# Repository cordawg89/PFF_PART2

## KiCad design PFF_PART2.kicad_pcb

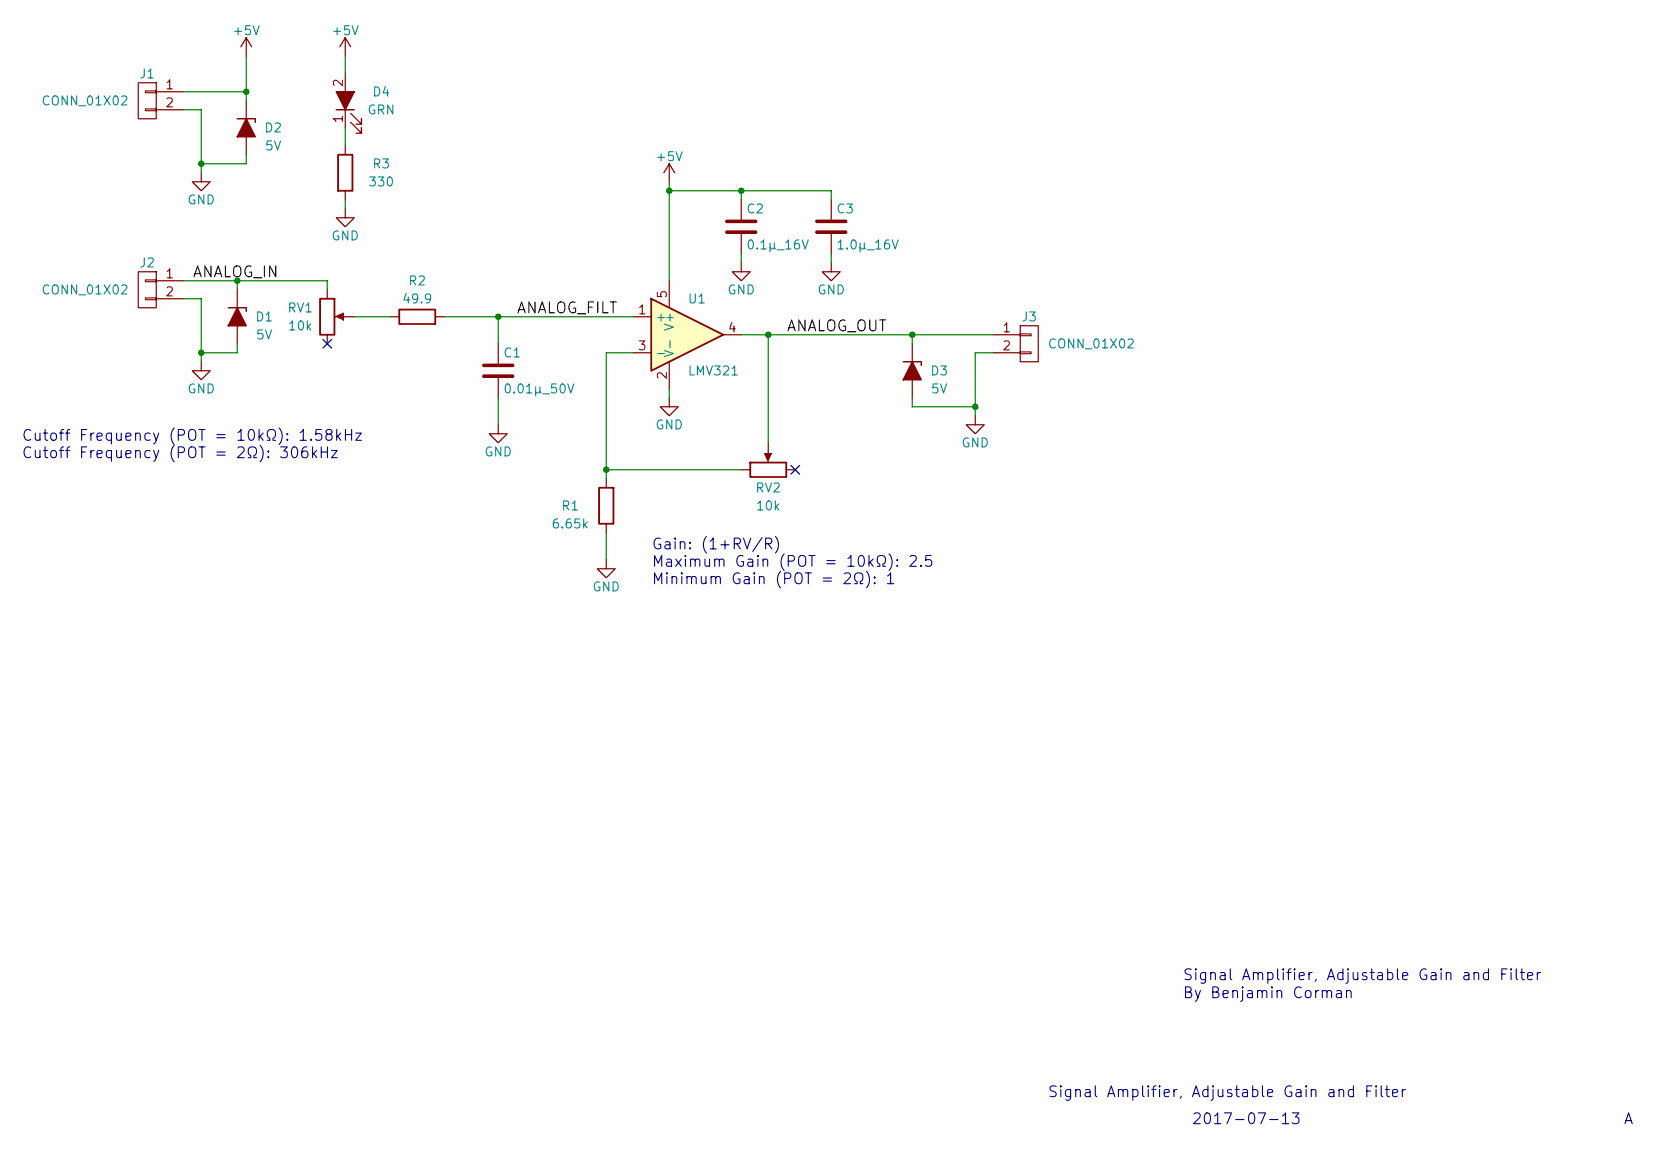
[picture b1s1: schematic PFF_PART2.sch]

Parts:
C1: 0.01µ_50V; C_0603; Manufacturer P/N CC0603KRX7R9BB103
C2: 0.1µ_16V; C_0603; Manufacturer P/N CC0603KRX7R7BB104
C3: 1.0µ_16V; C_0603; Manufacturer P/N CC0603KRX7R7BB105
D1, D2, D3: 5V; D_SOD-123F; Manufacturer P/N SMF5.0A
D4: GRN; LED_0603; Manufacturer P/N SML-D12M8WT86
J1, J2, J3: CONN_01X02; Pin_Header_Straight_1x02_Pitch2.54mm; Manufacturer P/N M20-9990245
R1: 6.65k; R_0603; Manufacturer P/N RC0603FR-076K65L
R2: 49.9; R_0603; Manufacturer P/N RC0603FR-0749R9L
R3: 330; R_0603; Manufacturer P/N RC0603FR-07330RL
RV1, RV2: 10k; Potentiometer_Trimmer_Bourns_3339H_Horizontal; Manufacturer P/N 3339H-1-103LF
U1: LMV321; SOT-23-5; Manufacturer P/N LMV321ILT

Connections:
+5V: C2.1, C3.1, D2.1 (K), D4.2 (A), J1.1, U1.5 (V+)
/ANALOG_FILT: C1.1, R2.2, U1.1 (+)
/ANALOG_IN: D1.1 (K), J2.1, RV1.1
/ANALOG_OUT: D3.1 (K), J3.1, RV2.2, U1.4
GND: C1.2, C2.2, C3.2, D1.2 (A), D2.2 (A), D3.2 (A), J1.2, J2.2, J3.2, R1.1, R3.2, U1.2 (V-)
unnamed: D4.1 (K), R3.1
unnamed: R1.2, RV2.1, U1.3 (-)
unnamed: R2.1, RV1.2

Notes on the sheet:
Cutoff Frequency (POT = 10kΩ): 1.58kHz Cutoff Frequency (POT = 2Ω): 306kHz
Gain: (1+RV/R) Maximum Gain (POT = 10kΩ): 2.5 Minimum Gain (POT = 2Ω): 1
Signal Amplifier, Adjustable Gain and Filter
By Benjamin Corman
2017-07-13

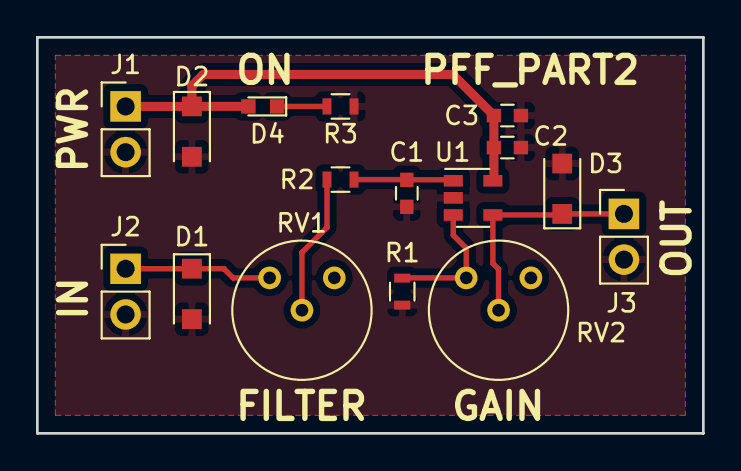
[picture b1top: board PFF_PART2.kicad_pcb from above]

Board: 2 copper layers, 37.0 x 22.0 mm, 16 parts (0 on the bottom side), 8 nets.

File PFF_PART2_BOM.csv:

Designator(s),QTY,Value,Manufacturer,Manufacturer P/N,Vendor,Vendor P/N
C1,1,0.01u_50V,Yageo,CC0603KRX7R9BB103,Digi-Key,311-1085-1-ND
C2,1,0.1u_50V,Yageo,CC0603KRX7R7BB104,Digi-Key,311-1088-1-ND
C3,1,1.0u_50V,Yageo,CC0603KRX7R7BB105,Digi-Key,311-1446-1-ND
"J1, J2, J3",3,CONN_01x02,Harwin,M20-9990245,Digi-Key,952-2261-ND
"D1, D2, D3",3,5V,Littelfuse,SMF5.0A,Digi-Key,F5748CT-ND
D4,1,GRN,Rohm Semiconductor,SML-D12M8WT86,Digi-Key,511-1578-1-ND
U1,1,LMV321,STMicroelectronics,LMV321ILT,Digi-Key,497-4941-1-ND
"RV1, RV2",2,10k,Bourns,3339H-1-103LF,Digi-Key,3339H-103LF-ND
R1,1,6.65k,Yageo,RC0603FR-076K65L,Digi-Key,311-6.65KHRCT-ND
R2,1,49.9,Yageo,RC0603FR-0749R9L,Digi-Key,311-49.9HRCT-ND
R3,1,330,Yageo,RC0603FR-07330RL,Digi-Key,311-330HRCT-ND

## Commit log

2017-07-14 Adding zip file for download
2017-07-14 adding all files
